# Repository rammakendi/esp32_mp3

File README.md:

"This is my first project, an MP3 capable of streaming music with an esp32"
inspiration - META GLASSES😊

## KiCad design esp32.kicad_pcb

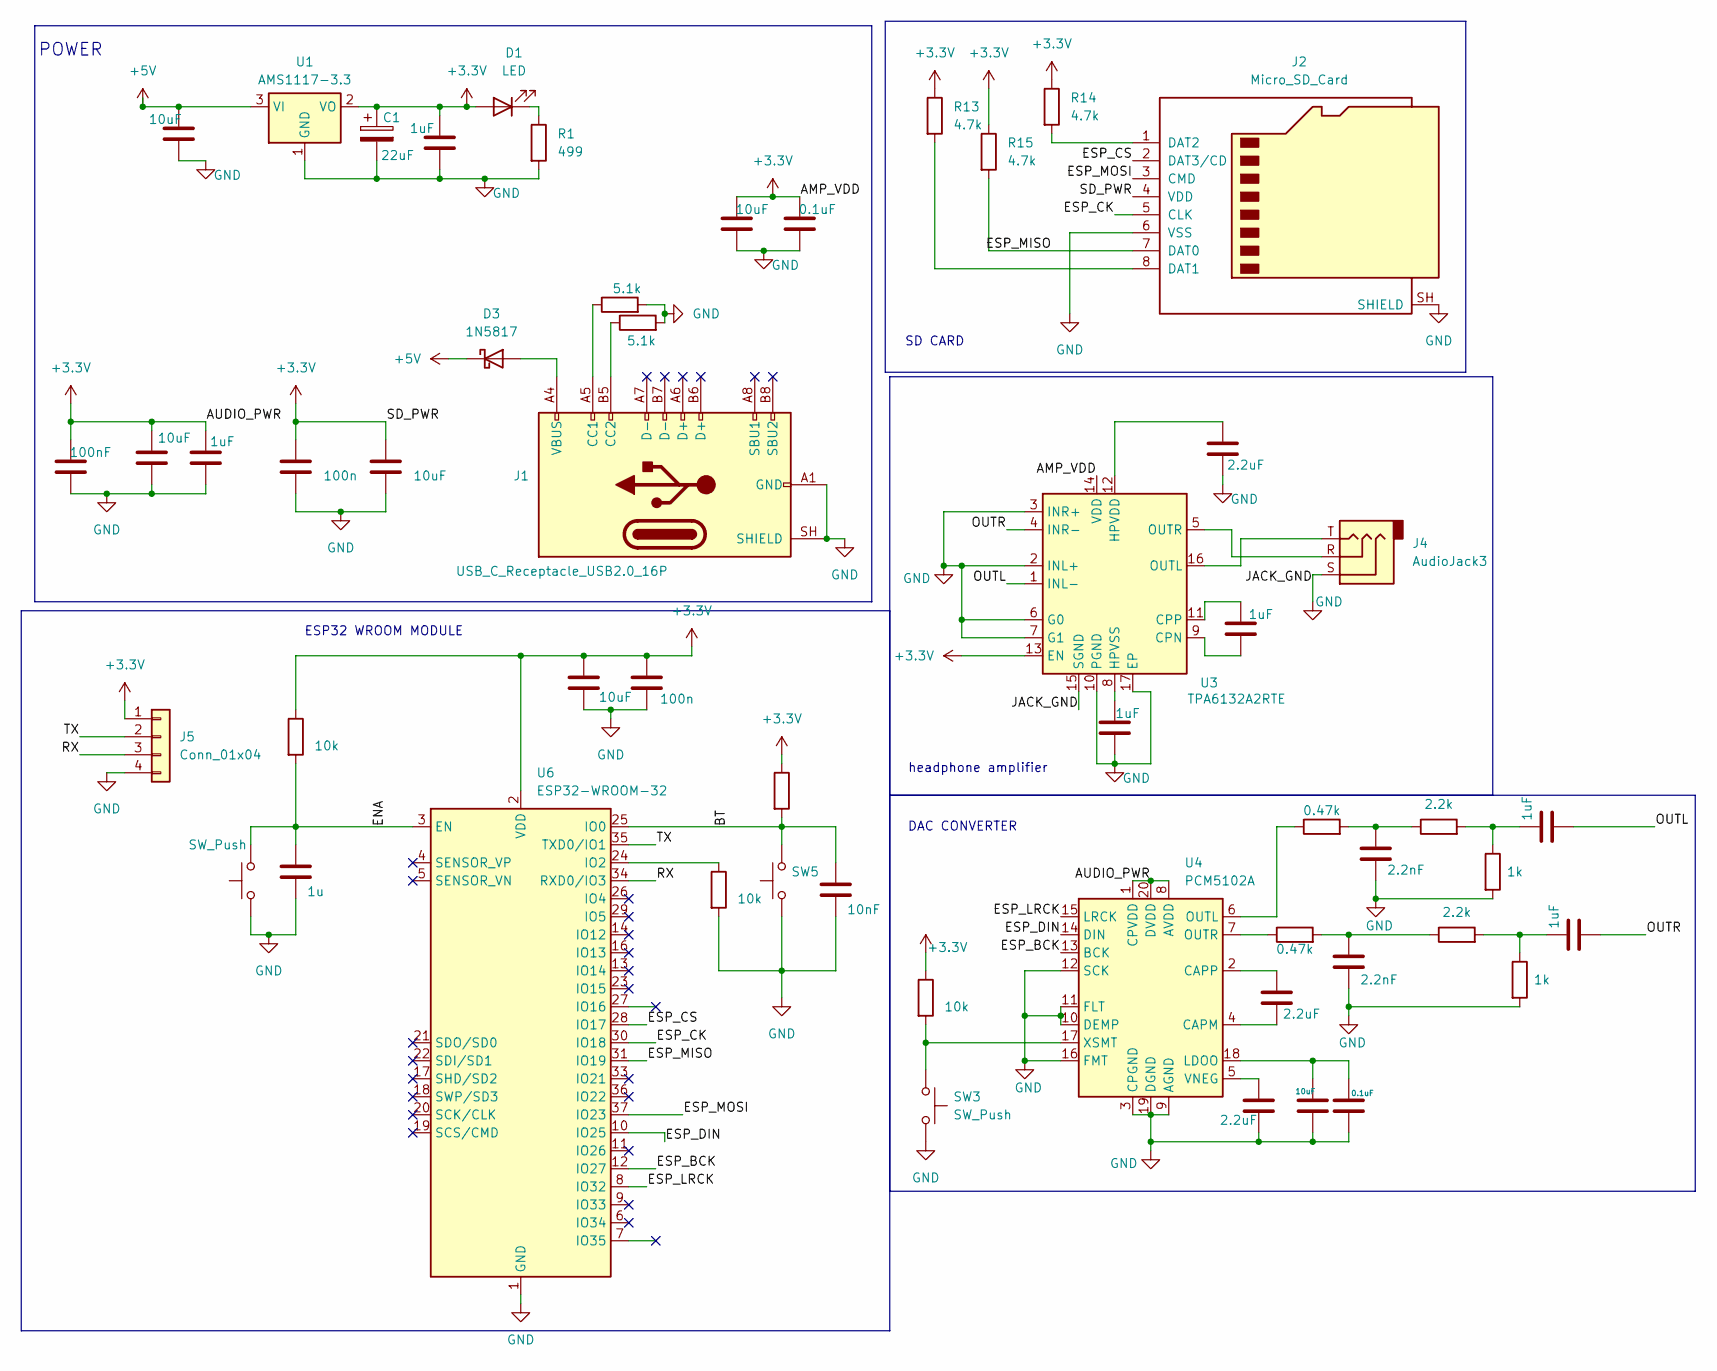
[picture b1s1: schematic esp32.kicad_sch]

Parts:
C1: 22uF; CP_EIA-3528-21_Kemet-B
C6, C19, C21, C38, C43: 10uF; C_0603_1608Metric
C7, C18: 100n; C_0603_1608Metric
C20: 100nF; C_0603_1608Metric
C22, C31, C35, C40, C42, C44: 1uF; C_0603_1608Metric
C23, C24: 2.2uF; C_0201_0603Metric
C25: 10uF; C_0201_0603Metric
C26: 0.1uF; C_0201_0603Metric
C29, C30: 2.2nF; C_0603_1608Metric
C32: 1u; C_0201_0603Metric
C34: 10nF; C_0201_0603Metric
C39: 0.1uF; C_0603_1608Metric
C41: 2.2uF; C_0603_1608Metric
D1: LED; LED_0603_1608Metric
D3: 1N5817; D_DO-41_SOD81_P10.16mm_Horizontal
J1: USB_C_Receptacle_USB2.0_16P; USB_C_Receptacle_HRO_TYPE-C-31-M-12
J2: Micro_SD_Card; microSD_HC_Wuerth_693072010801
J4: AudioJack3; Jack_3.5mm_CUI_SJ1-3523N_Horizontal
J5: Conn_01x04; PinHeader_1x04_P1.27mm_Vertical
R1: 499; R_0603_1608Metric
R7, R8: 5.1k; R_0603_1608Metric
R13, R14, R15: 4.7k; R_0201_0603Metric
R16, R24, R25, R26: 10k; R_0603_1608Metric
R17, R18: 0.47k; R_0603_1608Metric
R19, R23: 1k; R_0603_1608Metric
R21, R22: 2.2k; R_0603_1608Metric
SW3, SW4, SW5: SW_Push; SW_SPST_TL3305A
U1: AMS1117-3.3; SOT-223-3_TabPin2
U3: TPA6132A2RTE; WQFN-16-1EP_3x3mm_P0.5mm_EP1.6x1.6mm_ThermalVias
U4: PCM5102A; TSSOP-20_4.4x6.5mm_P0.65mm
U6: ESP32-WROOM-32

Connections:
+3.3V: C1.1, C6.1, C7.1, C18.1, C19.1, C20.1, C21.1, C22.1, C38.1, C39.1, C44.1, D1.2 (A), J2.4 (VDD), J5.1, R13.1, R14.1, R15.1, R16.1, R24.1, R26.1, U1.2 (VO), U3.13 (EN), U3.14 (VDD), U4.1 (CPVDD), U4.8 (AVDD), U4.20 (DVDD), U6.2 (VDD)
+5V: C43.1, D3.1 (K), U1.3 (VI)
/BT: C34.1, R26.2, SW5.2, U6.25 (IO0)
/ENA: C32.1, R24.2, SW4.2, U6.3 (EN)
/ESP_BCK: U4.13 (BCK), U6.12 (IO27)
/ESP_CK: J2.5 (CLK), U6.30 (IO18)
/ESP_CS: J2.2 (DAT3/CD), U6.28 (IO17)
/ESP_DIN: U4.14 (DIN), U6.10 (IO25)
/ESP_LRCK: U4.15 (LRCK), U6.8 (IO32)
/ESP_MISO: J2.7 (DAT0), R15.2, U6.31 (IO19)
/ESP_MOSI: J2.3 (CMD), U6.37 (IO23)
/OUTL: C35.2, U3.1 (INL-)
/OUTR: C31.2, U3.4 (INR-)
/RX: J5.3, U6.34 (RXD0/IO3)
/TX: J5.2, U6.35 (TXD0/IO1)
GND: C1.2, C6.2, C7.2, C18.2, C19.2, C20.2, C21.2, C22.2, C24.2, C25.2, C26.2, C29.2, C30.2, C32.2, C34.2, C38.2, C39.2, C40.2, C41.2, C43.2, C44.2, J1.A1 (GND), J1.A12 (GND), J1.B1 (GND), J1.B12 (GND), J1.SH (SHIELD), J2.6 (VSS), J2.SH (SHIELD), J4.S, J5.4, R1.2, R7.2, R8.2, R19.2, R23.2, R25.2, SW3.2, SW4.1, SW5.1, U1.1 (GND), U3.2 (INL+), U3.3 (INR+), U3.6 (G0), U3.7 (G1), U3.10 (PGND), U3.15 (SGND), U3.17 (EP), U4.3 (CPGND), U4.9 (AGND), U4.10 (DEMP), U4.11 (FLT), U4.12 (SCK), U4.16 (FMT), U4.19 (DGND), U6.1 (GND), U6.15 (GND), U6.38 (GND), U6.39 (GND)
unnamed: C29.1, R18.2, R22.1
unnamed: C30.1, R17.2, R21.1
unnamed: C31.1, R19.1, R21.2
unnamed: C35.1, R22.2, R23.1
unnamed: D1.1 (K), R1.1
unnamed: D3.2 (A), J1.A4 (VBUS), J1.A9 (VBUS), J1.B4 (VBUS), J1.B9 (VBUS)
unnamed: J1.A5 (CC1), R7.1
unnamed: J1.B5 (CC2), R8.1
unnamed: J2.8 (DAT1), R13.2
unnamed: J2.1 (DAT2), R14.2
unnamed: C42.2, U3.9 (CPN)
unnamed: C42.1, U3.11 (CPP)
unnamed: C41.1, U3.12 (HPVDD)
unnamed: C40.1, U3.8 (HPVSS)
unnamed: J4.T, U3.16 (OUTL)
unnamed: J4.R, U3.5 (OUTR)
unnamed: C23.2, U4.4 (CAPM)
unnamed: C23.1, U4.2 (CAPP)
unnamed: C25.1, C26.1, U4.18 (LDOO)
unnamed: R18.1, U4.6 (OUTL)
unnamed: R17.1, U4.7 (OUTR)
unnamed: C24.1, U4.5 (VNEG)
unnamed: R16.2, SW3.1, U4.17 (XSMT)
unnamed: R25.1, U6.24 (IO2)

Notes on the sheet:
headphone amplifier
POWER
DAC CONVERTER
SD CARD
ESP32 WROOM MODULE

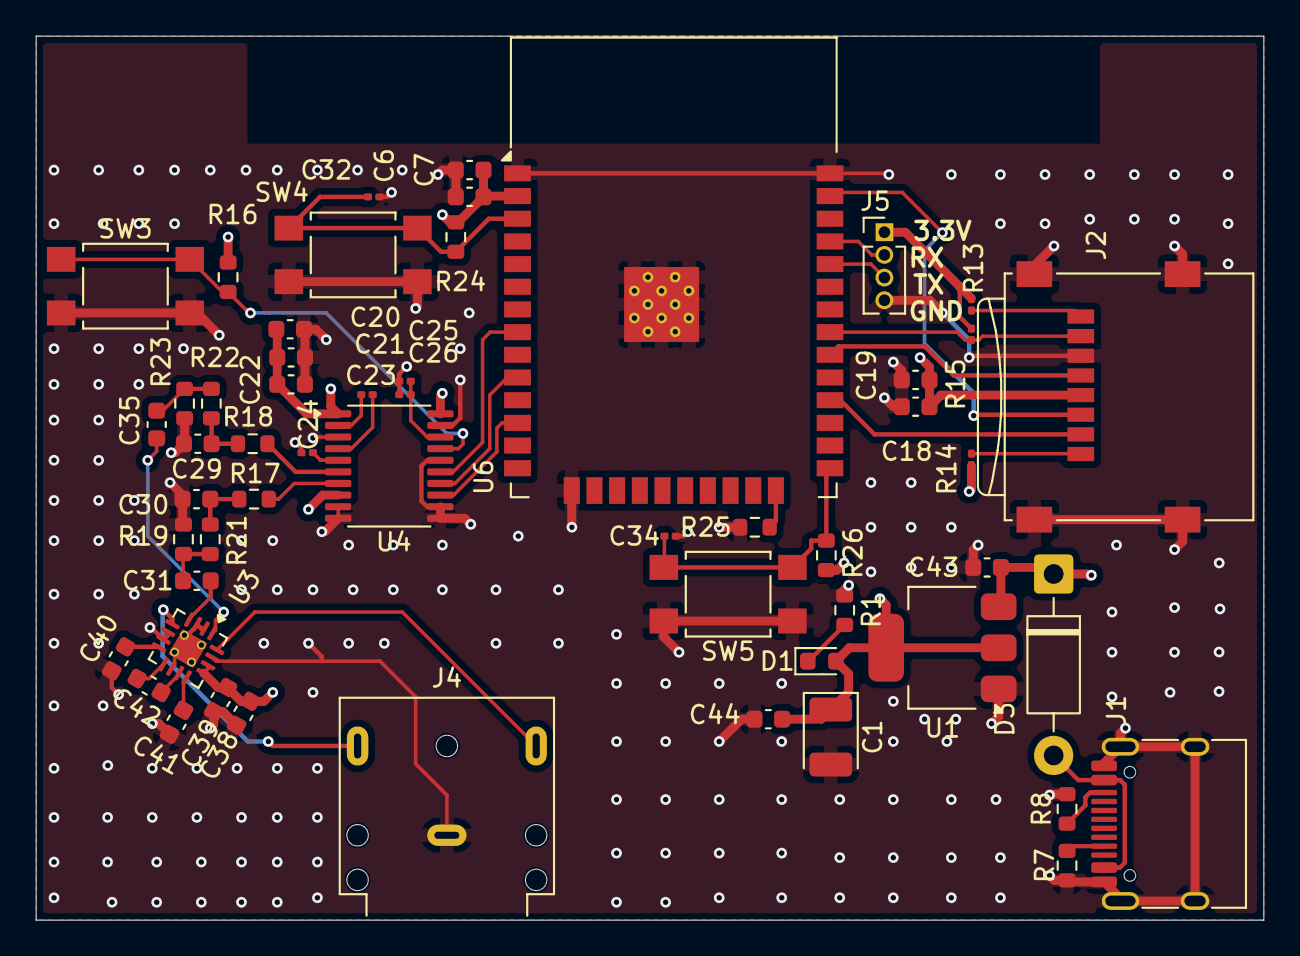
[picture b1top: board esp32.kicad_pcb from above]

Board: 4 copper layers, 68.8 x 49.5 mm, 54 parts (0 on the bottom side), 40 nets.
